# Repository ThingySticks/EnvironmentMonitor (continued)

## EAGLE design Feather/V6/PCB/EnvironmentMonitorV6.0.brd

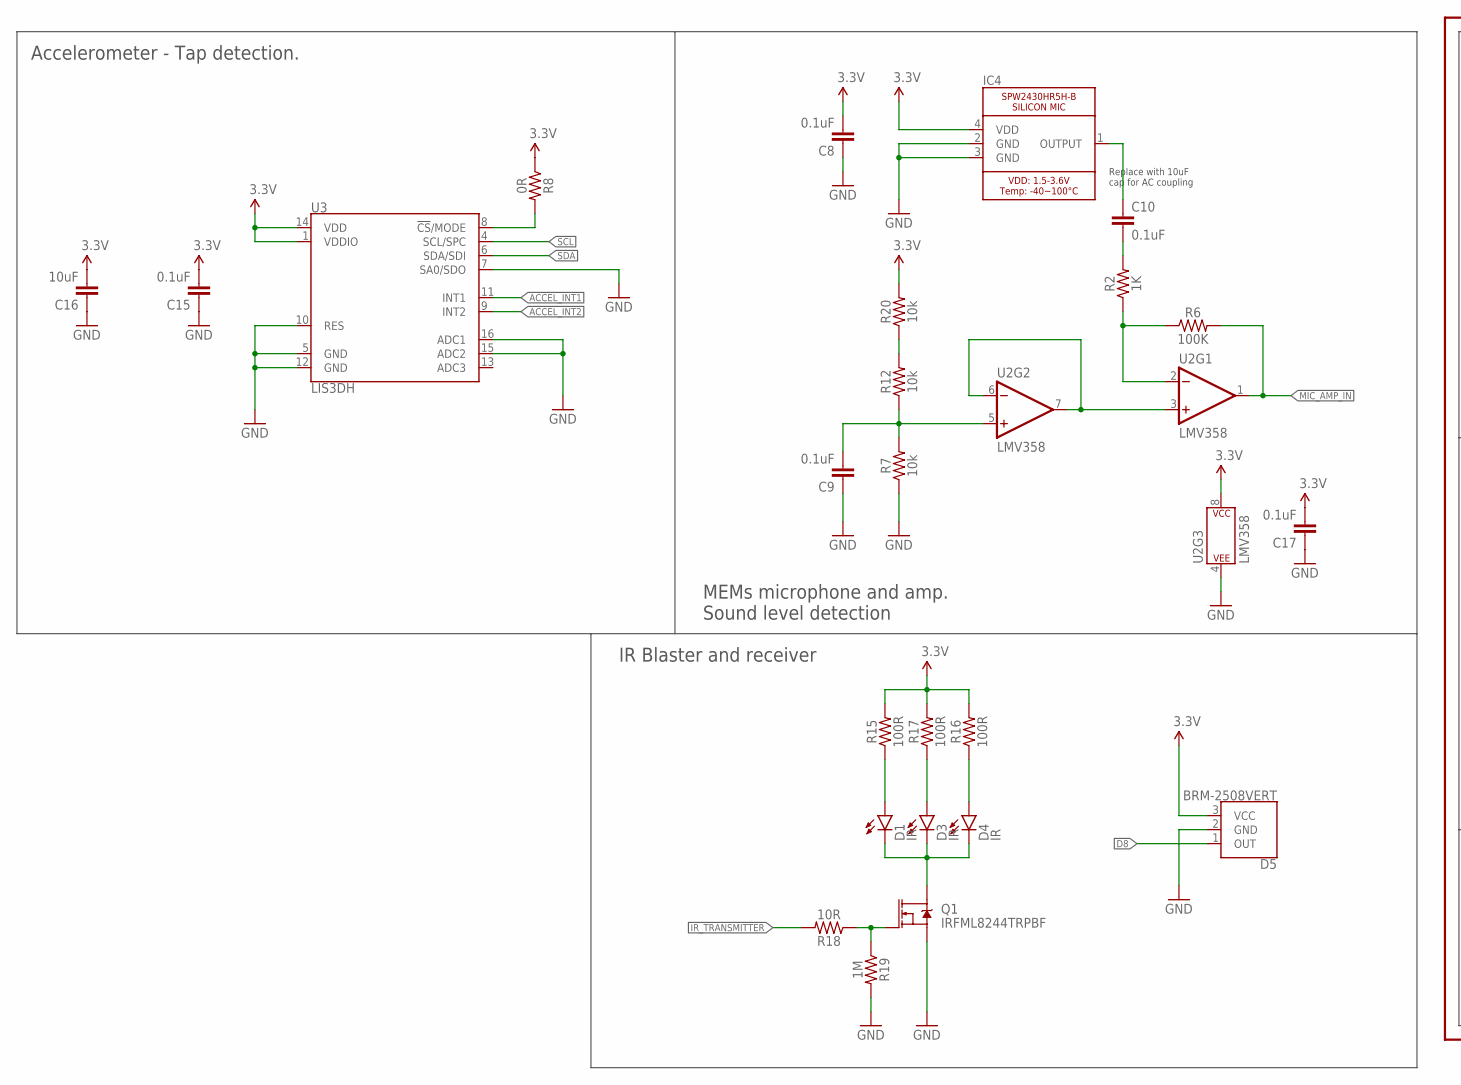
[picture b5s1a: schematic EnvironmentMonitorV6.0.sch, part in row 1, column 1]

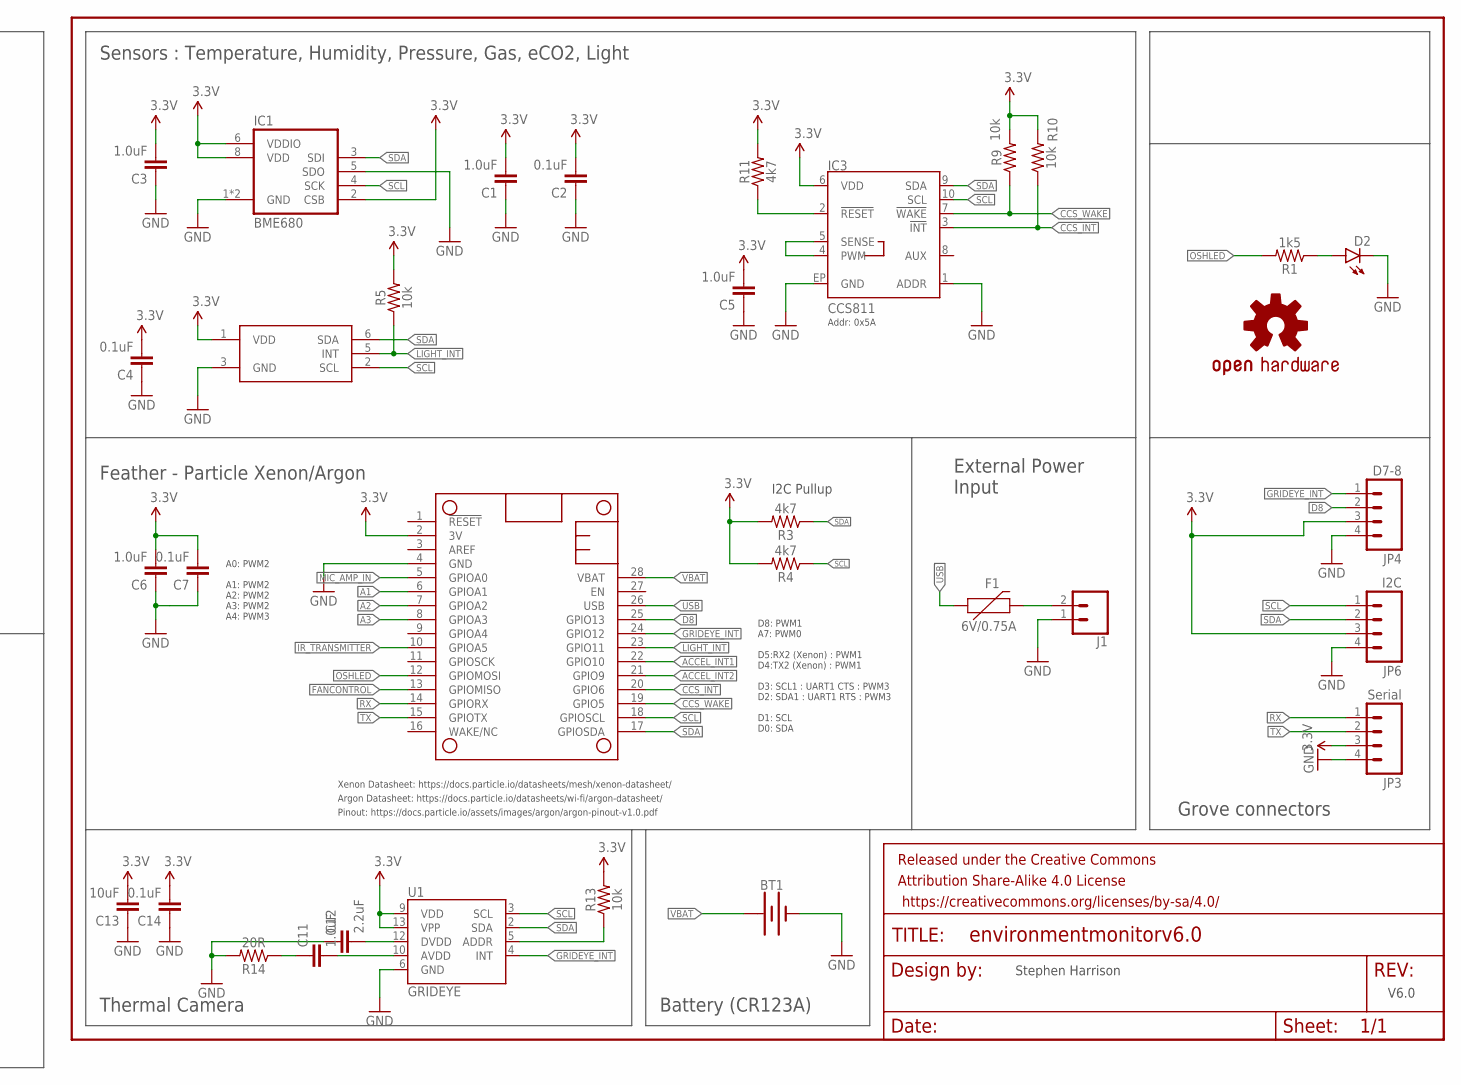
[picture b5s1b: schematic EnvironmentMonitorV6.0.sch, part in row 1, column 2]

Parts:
BT1: BATTERY-16340; BATTERY_16340-HOLDER
C1, C3, C5, C6, C11: 1.0uF; 0805-CAP
C2, C4, C7, C8, C9, C10, C14, C15, C17: 0.1uF; 0805-CAP
C12: 2.2uF; 0805-CAP; FARNELL 2070473
C13, C16: 10uF; 0805-CAP
D1, D3, D4: IR; LED-1206; FARNELL 2313501
D2: LED1206-BOTTOM; LED-1206-BOTTOM
D5: BRM-2508VERT; BRM-2508_VERT
F1: 6V/0.75A; 1206; FARNELL 2786571
FRAME1: FRAME-LETTER; CREATIVE_COMMONS
IC1: BME680
IC2: TCS3472; FN-6
IC3: CCS811; LGA10
IC4: SPW2430HR5H-B
IC5: FEATHERWING_NODIM; FEATHERWING_DIM
J1: CONN_02-JST-2MM-SMT; JST-2-SMD
JP3: Serial; JST-4-PTH-VERT
JP4: D7-8; JST-4-PTH-VERT
JP6: I2C; JST-4-PTH-VERT
LOGO1: OSHW-LOGOM; OSHW-LOGO-M
Q1: IRFML8244TRPBF; SOT23-3; FARNELL 1857298
R1: 1k5; 0805
R2: 1K; 0805
R3, R4, R11: 4k7; 0805
R5, R7, R9, R10, R12, R13, R20: 10k; 0805
R6: 100K; 0805
R8: 0R; 0805
R14: 20R; 0805; FARNELL 2447604
R15, R16, R17: 100R; 0805
R18: 10R; 0805
R19: 1M; 0805; FARNELL 2129354
U1: GRIDEYE; GRIDEYE-AMG88
U2: LMV358; SO08
U3: LIS3DH; LGA-16-3X3

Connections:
3.3V: C1.2, C2.2, C3.2, C4.2, C5.2, C6.2, C7.2, C8.2, C13.2, C14.2, C15.2, C16.2, C17.2, D5.3 (VCC), IC1.2 (CSB), IC1.6 (VDDIO), IC1.8 (VDD), IC2.1 (VDD), IC3.6 (VDD), IC4.4 (VDD), IC5.2 (3V), JP3.3, JP4.3, JP6.3, R3.2, R4.2, R5.2, R8.1, R9.2, R10.2, R11.2, R13.2, R15.2, R16.2, R17.2, R20.2, U1.9 (VDD), U1.13 (VPP), U2.8 (P$V+), U3.1 (VDDIO), U3.14 (VDD)
A1: IC5.6 (GPIOA1)
A2: IC5.7 (GPIOA2)
A3: IC5.8 (GPIOA3)
ACCEL_INT1: IC5.22 (GPIO10), U3.11 (INT1)
ACCEL_INT2: IC5.21 (GPIO9), U3.9 (INT2)
CCS8_RESET: IC3.2 (!RESET!), R11.1
CCS_INT: IC3.3 (!INT!), IC5.20 (GPIO6), R10.1
CCS_WAKE: IC3.7 (!WAKE!), IC5.19 (GPIO5), R9.1
D8: D5.1 (OUT), IC5.25 (GPIO13), JP4.2
FANCONTROL: IC5.13 (GPIOMISO)
GND: BT1.P$2 (-), C1.1, C2.1, C3.1, C4.1, C5.1, C6.1, C7.1, C8.1, C9.1, C12.1, C13.1, C14.1, C15.1, C16.1, C17.1, D2.C, D5.2 (GND), IC1.1 (GND), IC1.5 (SDO), IC1.7 (GND), IC2.3 (GND), IC3.1 (ADDR), IC3.EP (GND), IC4.2 (GND), IC4.3 (GND), IC5.4 (GND), J1.1 (2), JP3.4, JP4.4, JP6.4, Q1.2 (S), R7.1, R14.2, R19.2, U1.6 (GND), U2.4 (P$V-), U3.5 (GND), U3.7 (SA0/SDO), U3.10 (RES), U3.12 (GND), U3.15 (ADC2), U3.16 (ADC1)
GRIDEYE_INT: IC5.24 (GPIO12), JP4.1, U1.4 (INT)
IR_TRANSMITTER: IC5.10 (GPIOA5), R18.2
LIGHT_INT: IC2.5 (INT), IC5.23 (GPIO11), R5.1
MIC_AMP_IN: IC5.5 (GPIOA0), R6.2, U2.1 (OUT)
unnamed: R2.1, R6.1, U2.2 (-IN)
unnamed: D1.A, R15.1
unnamed: IC3.4 (PWM), IC3.5 (SENSE)
unnamed: C10.2, R2.2
unnamed: U2.3 (+IN), U2.6 (-IN), U2.7 (OUT)
unnamed: D2.A, R1.1
unnamed: C10.1, IC4.1 (OUTPUT)
unnamed: D3.A, R17.1
unnamed: C9.2, R7.2, R12.1, U2.5 (+IN)
unnamed: R13.1, U1.5 (ADDR)
unnamed: D1.C, D3.C, D4.C, Q1.3 (D)
unnamed: R12.2, R20.1
unnamed: D4.A, R16.1
unnamed: C12.2, U1.12 (DVDD)
unnamed: C11.2, U1.10 (AVDD)
unnamed: C11.1, R14.1
unnamed: Q1.1 (G), R18.1, R19.1
unnamed: F1.2, J1.2 (1)
unnamed: R8.2, U3.8 (!CS!/MODE)
OSHLED: IC5.12 (GPIOMOSI), R1.2
RX: IC5.14 (GPIORX), JP3.1
SCL: IC1.4 (SCK), IC2.2 (SCL), IC3.10 (SCL), IC5.18 (GPIOSCL), JP6.1, R4.1, U1.3 (SCL), U3.4 (SCL/SPC)
SDA: IC1.3 (SDI), IC2.6 (SDA), IC3.9 (SDA), IC5.17 (GPIOSDA), JP6.2, R3.1, U1.2 (SDA), U3.6 (SDA/SDI)
TX: IC5.15 (GPIOTX), JP3.2
USB: F1.1, IC5.26 (USB)
VBAT: BT1.P$1 (+), IC5.28 (VBAT)

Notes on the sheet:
I2C Pullup
V6.0
Stephen Harrison
Xenon Datasheet: https://docs.particle.io/datasheets/mesh/xenon-datasheet/
Argon Datasheet: https://docs.particle.io/datasheets/wi-fi/argon-datasheet/
Pinout: https://docs.particle.io/assets/images/argon/argon-pinout-v1.0.pdf
A0: PWM2 A1: PWM2 A2: PWM2 A3: PWM2 A4: PWM3
D8: PWM1 A7: PWM0 D5:RX2 (Xenon) : PWM1 D4:TX2 (Xenon) : PWM1 D3: SCL1 : UART1 CTS : PWM3 D2: SDA1 : UART1 RTS : PWM3 D1: SCL D0: SDA
Replace with 10uF cap for AC coupling
Addr: 0x5A
Accelerometer - Tap detection.
MEMs microphone and amp. Sound level detection
IR Blaster and receiver
Thermal Camera
Battery (CR123A)
Grove connectors
Feather - Particle Xenon/Argon
Sensors : Temperature, Humidity, Pressure, Gas, eCO2, Light
External Power Input

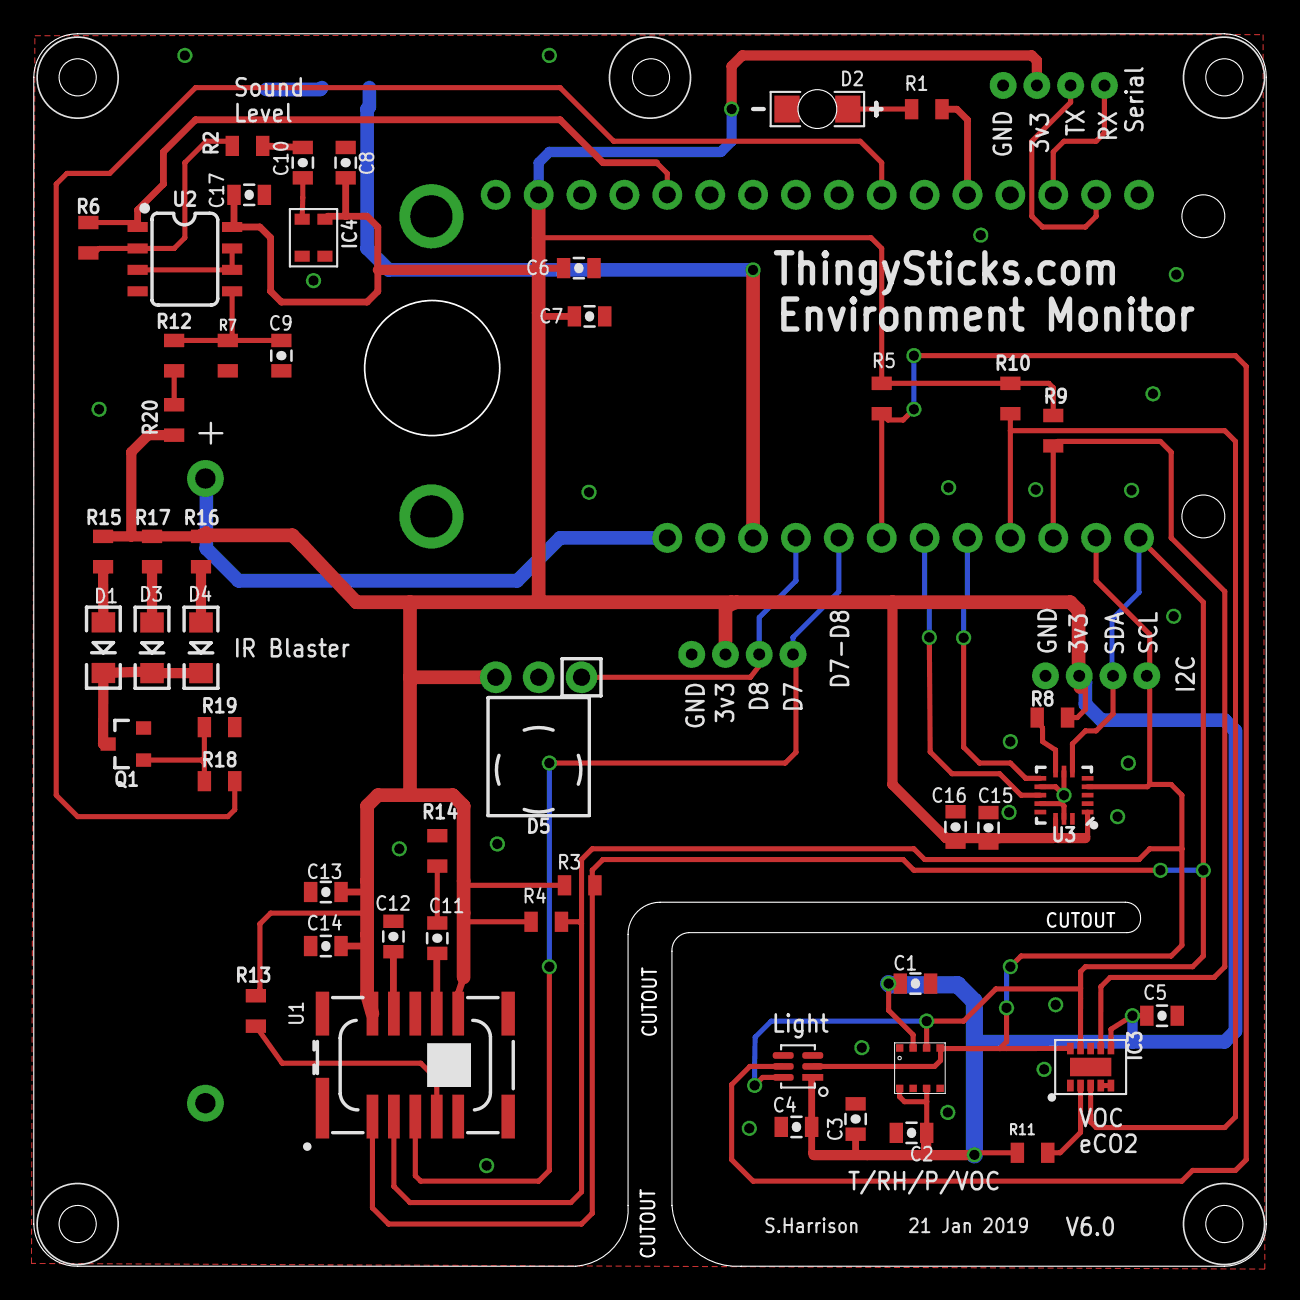
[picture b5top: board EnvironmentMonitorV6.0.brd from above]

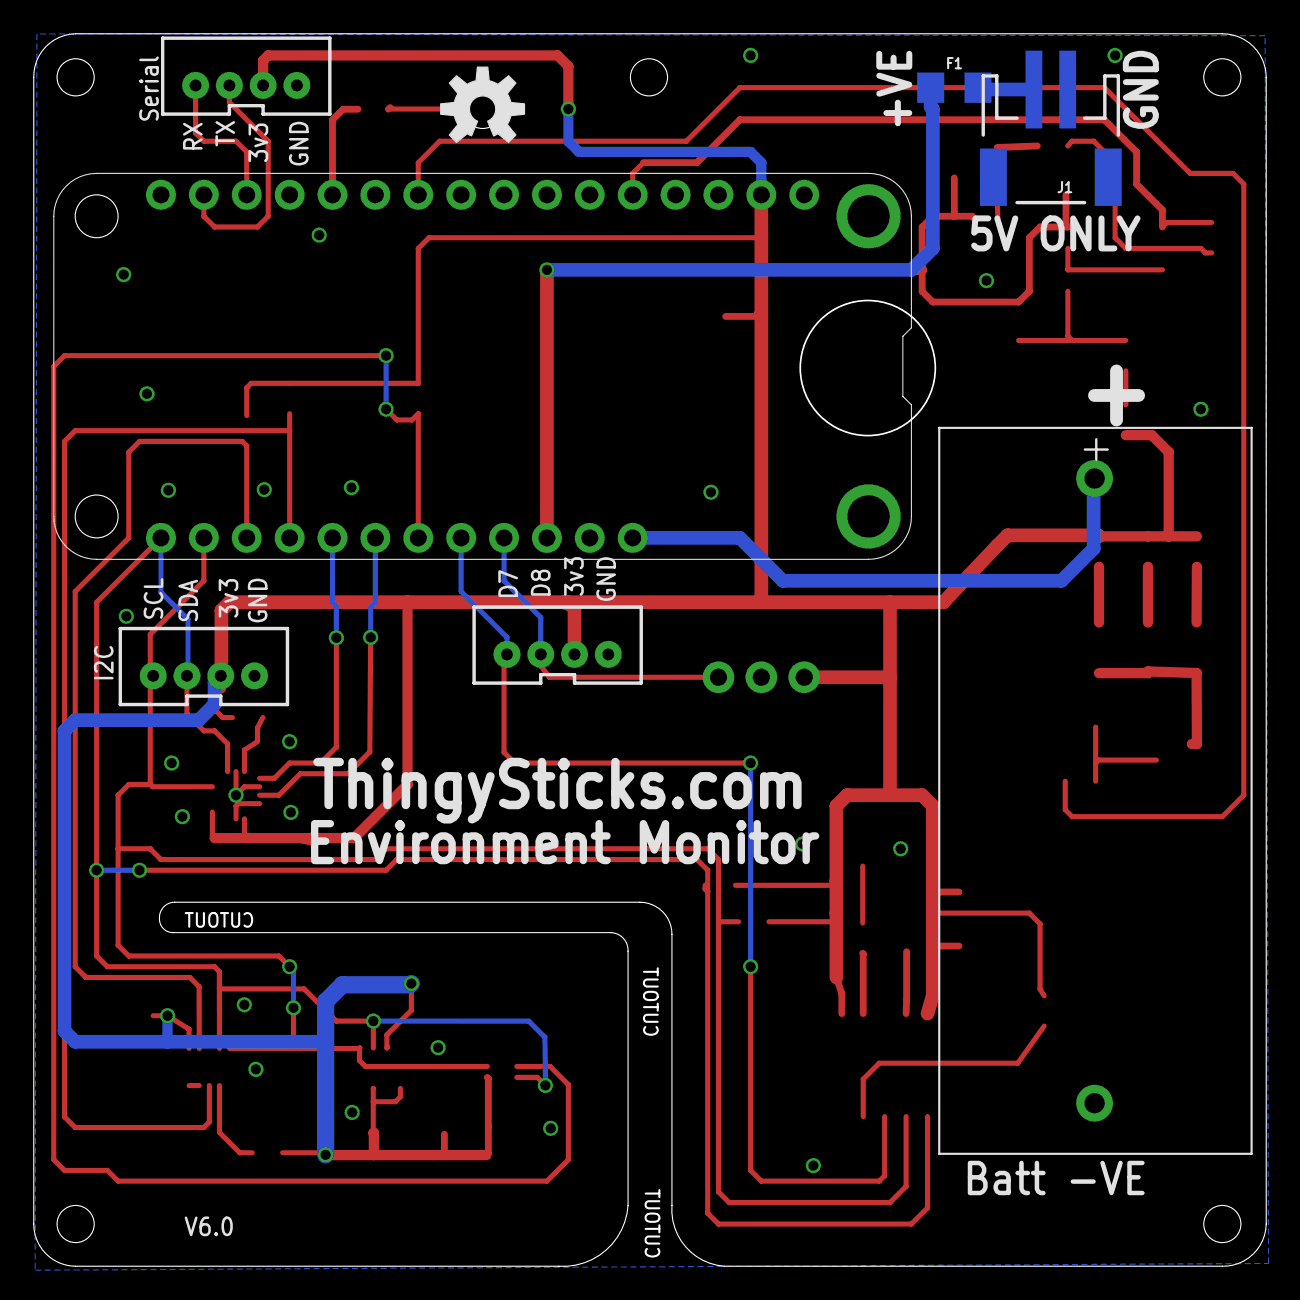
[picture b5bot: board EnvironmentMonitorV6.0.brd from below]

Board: 2 copper layers, 73.0 x 73.0 mm, 59 parts (8 on the bottom side), 38 nets.

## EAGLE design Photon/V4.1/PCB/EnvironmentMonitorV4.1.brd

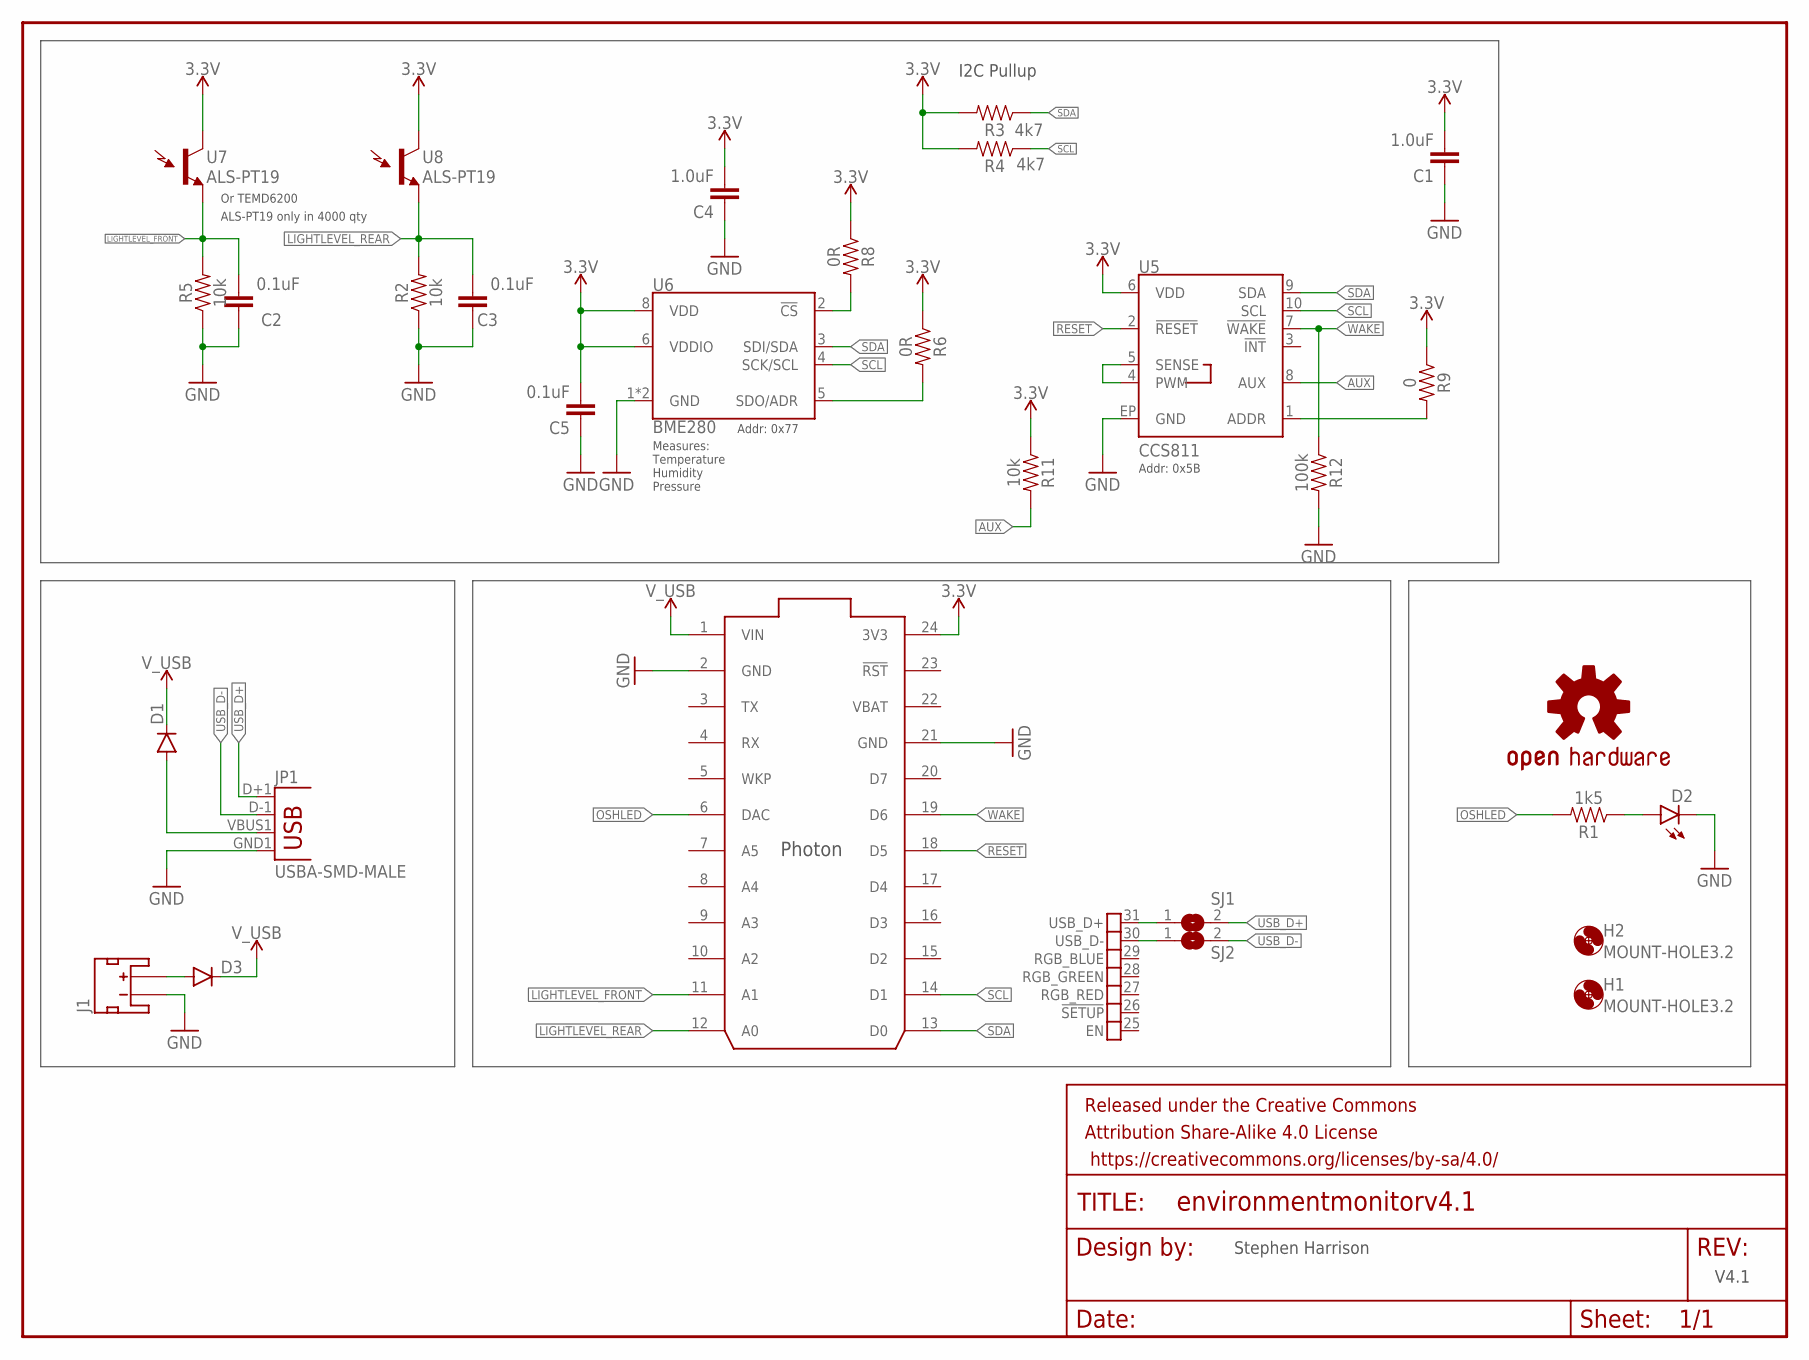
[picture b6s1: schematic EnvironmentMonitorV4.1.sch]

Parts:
C1, C4: 1.0uF; 0805-CAP
C2, C3, C5: 0.1uF; 0805-CAP
D1, D3: DIODESMA; SMA-DIODE
D2: LED1206-BOTTOM; LED-1206-BOTTOM
FRAME1: FRAME-LETTER; CREATIVE_COMMONS
H1, H2: MOUNT-HOLE3.2; 3,2
J1: JST_2MM_MALE; JST-2-SMD
JP1: USBA-SMD-MALE; USB-A-SMT-MALE
LOGO1: OSHW-LOGOM; OSHW-LOGO-M
R1: 1k5; 0805
R2, R5, R11: 10k; 0805
R3, R4: 4k7; 0805
R6, R8: 0R; 0805
R9: 0; 0805
R12: 100k; 0805
SJ1, SJ2: SJ
U5: CCS811; LGA10
U6: BME280; LGA-8-2.5X2.5
U7, U8: ALS-PT19
U$1: PHOTON_SMD

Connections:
3.3V: C1.2, C4.2, C5.2, R3.2, R4.2, R6.1, R8.1, R9.1, R11.1, U5.6 (VDD), U6.6 (VDDIO), U6.8 (VDD), U7.C (C1), U8.C (C1), U$1.24 (3V3)
AUX: R11.2, U5.8 (AUX)
BME280_CS: R8.2, U6.2 (!CS)
GND: C1.1, C2.1, C3.1, C4.1, C5.1, D2.C, J1.1 (-), JP1.GND1 (GND), R2.1, R5.1, R12.2, U5.EP (GND), U6.1 (GND), U6.7 (GND), U$1.2 (GND), U$1.21 (GND)
LIGHTLEVEL_FRONT: C2.2, R5.2, U7.E (E1), U$1.11 (A1)
LIGHTLEVEL_REAR: C3.2, R2.2, U8.E (E1), U$1.12 (A0)
unnamed: SJ1.1, U$1.31 (USB_D+)
unnamed: SJ2.1, U$1.30 (USB_D-)
unnamed: R6.2, U6.5 (SDO/ADR)
unnamed: D3.A, J1.2 (+)
unnamed: D1.A, JP1.VBUS1 (VBUS)
unnamed: D2.A, R1.1
unnamed: R9.2, U5.1 (ADDR)
NTC_SENSE: U5.4 (PWM), U5.5 (SENSE)
OSHLED: R1.2, U$1.6 (DAC)
RESET: U5.2 (!RESET!), U$1.18 (D5)
SCL: R4.1, U5.10 (SCL), U6.4 (SCK/SCL), U$1.14 (D1)
SDA: R3.1, U5.9 (SDA), U6.3 (SDI/SDA), U$1.13 (D0)
USB_D+: JP1.D+1 (D+), SJ1.2
USB_D-: JP1.D-1 (D-), SJ2.2
VBAT: U$1.22 (VBAT)
V_USB: D1.C, D3.C, U$1.1 (VIN)
WAKE: R12.1, U5.7 (!WAKE!), U$1.19 (D6)

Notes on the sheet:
I2C Pullup
V4.1
Stephen Harrison
Or TEMD6200
ALS-PT19 only in 4000 qty
Measures: Temperature Humidity Pressure
Addr: 0x77
Addr: 0x5B

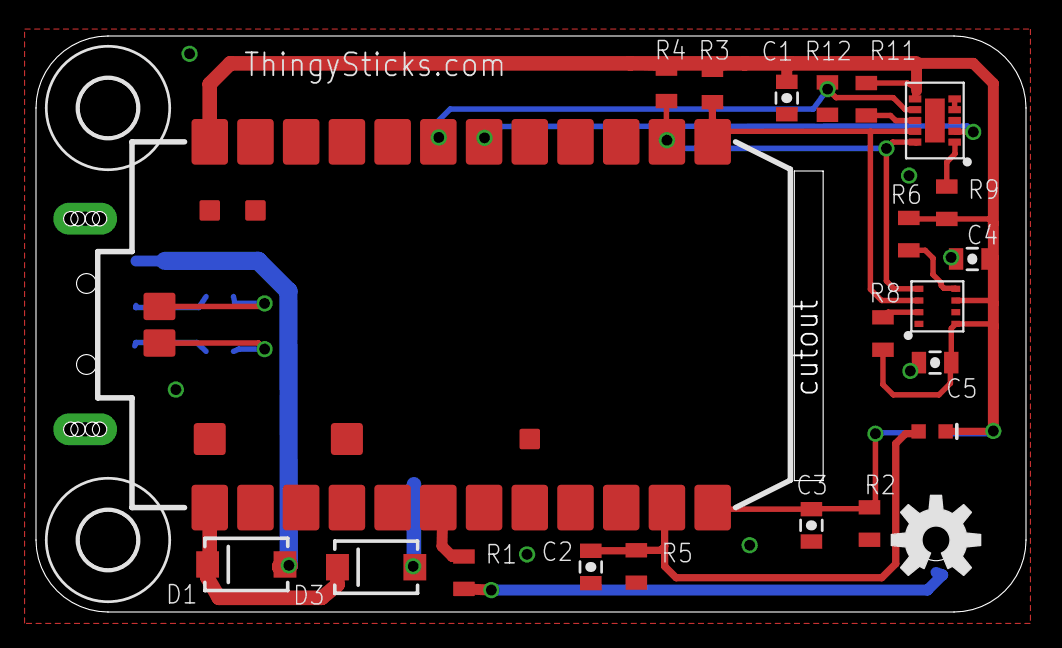
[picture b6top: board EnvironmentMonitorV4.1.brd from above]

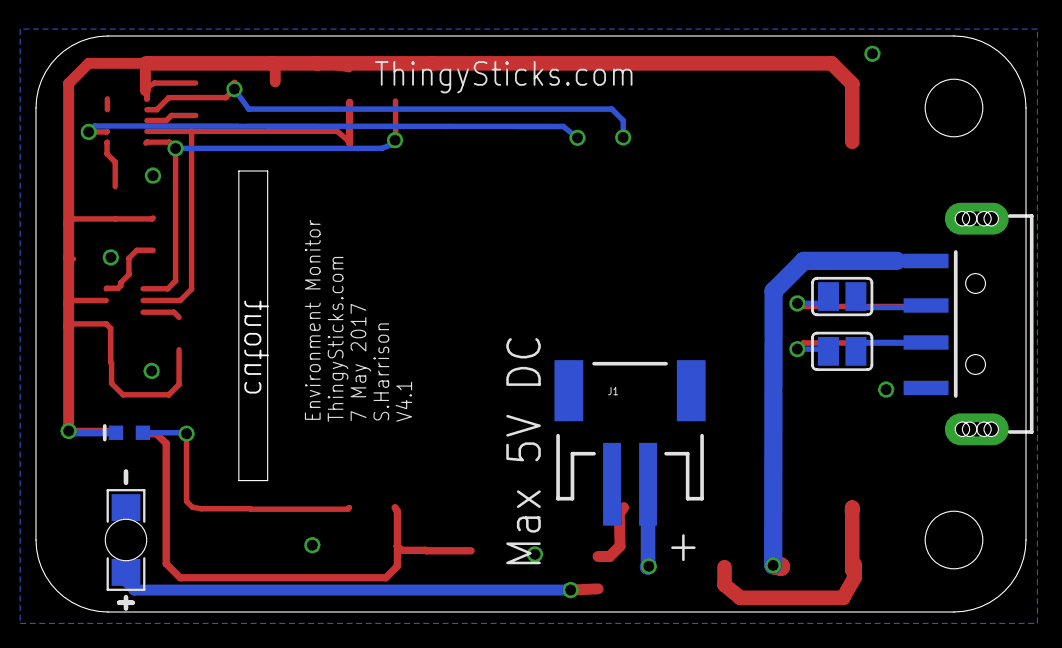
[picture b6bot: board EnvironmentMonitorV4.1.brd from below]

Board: 2 copper layers, 55.0 x 32.0 mm, 31 parts (6 on the bottom side), 22 nets.
